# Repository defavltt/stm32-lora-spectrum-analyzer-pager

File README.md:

# STM32 based LoRa spectrum analyzer & pager

<!--  -->

## Features

 - Sending and receiving messages through LoRa
 
 - Configuring most of the RFM95's settings
 
 - Spectrum analyzer
 
 - Direct view of RFM95's registers
 
 - Battery measurement
 
 - Backlight
 
 - Vibration
 
 - Sleep modes
 
## Operation

 - Main menu is opened by pressing any button except multi key and escape

 - Stored messages can be seen by pressing multi key

 - Pressing and holding up / down automatically repeats the button

 - Waking up is done by pressing escape

 - Backlight is turned on / off by pressing and holding enter

## Menu description

### *All 10 menus (with the last one being an optional clock)*

### *Send message*

 - Screen is split into two halves
   - Text field
   - Scrollable keyboard with SEND / CLEAR / BACKSPACE buttons at the bottom

### *Display settings*

 - Backlight mode - timeout / no timeout (will not go to sleep) / on startup (turn backlight on when starting up)
 - Adjust contrast

### *RF settings*

 - Setting frequency
   - Select a digit to change by entering in the option and moving the digit cursor left / right
 - Continuous TX - doesnt transmit actual data, used for testing other devices

### *Feedback*

 - Select ringing type when a message is received - silent / single beep / beep & vibration / only vibration
 - Select key press feedback - silent / only click / click & vibration / only vibration

### *Sleep settings*

 - Enable / disable sleep
 - Enable / disable receiving (when enabled, device wakes up every 5 seconds to listen for a incoming message)

### *Battery level*

 - Shows battery level in volts

### *Spectrum analyzer*

 - Marker indicates RSSI for center frequency
 - 4 levels of vertical zooming
 - Navigation through parameters is done by pressing enter
 - Editing starting and ending frequency of the window
   - Up / down adjusts frequency by 1
   - Left / right adjusts frequency by 5
 - Showing parameters and/or marker is done by pressing multi key

### *Registers debug*

 - Top left number showing address of the first register of the group
 - Top right is showing current selected register in binary format
 - Values at left are registers in HEX format
 - Values at right are the addresses corresponding to the registers
 - Navigating the 8 register group is done by pressing up / down
 - Navigating outside of the group is done by pressing left / right

### *Save settings*

 - Saves settings into flash (don't overdo it to prevent flash memory wear)

### *Time and date*

 - Setting time
   - Select hour / minute by entering in the option, moving the digit cursor left / right and changing it by pressing up / down
 - Setting date
   - Select day / month / year by entering in the option, moving the digit cursor left / right and changing it by pressing up / down
 - Confirm by pressing enter on set time / date

 - *Requires an i2c clock board(MCP7940)*  

## Hardware

 - Parts
   - RFM95/SX1276 board
   - Tri-T D22-5003 B01 lcd screen (ks0713 driver)
   - STM32F103C8
   - 8Mhz crystal resonator
   - MCP1700 / MCP1703 3.3v regulator
   - AP2301 P channel MOSFETs used to drive vibrator and buzzer

Double sided board (bottom side freehand drawn with a permanent marker) with some wire jumpers required. Pads for keyboard, screen and optional serial are left. Parts from MT3608 are used for the backlight 8.2v power (only if the same screen is used - Tri-T D22-5003 B01 / driver - ks0713). Using a connector for plugging in an external antenna or a PA is encouraged.

This project uses:  
[Arduino Core STM32](https://github.com/stm32duino/Arduino_Core_STM32)  
[STM32 Low Power](https://github.com/stm32duino/STM32LowPower)  
[u8g2](https://github.com/olikraus/u8g2)  
a modified version of [RadioHead](https://www.airspayce.com/mikem/arduino/RadioHead)  
a modified version of [MCP7940](https://github.com/Zanduino/MCP7940)  

*MCX connector*

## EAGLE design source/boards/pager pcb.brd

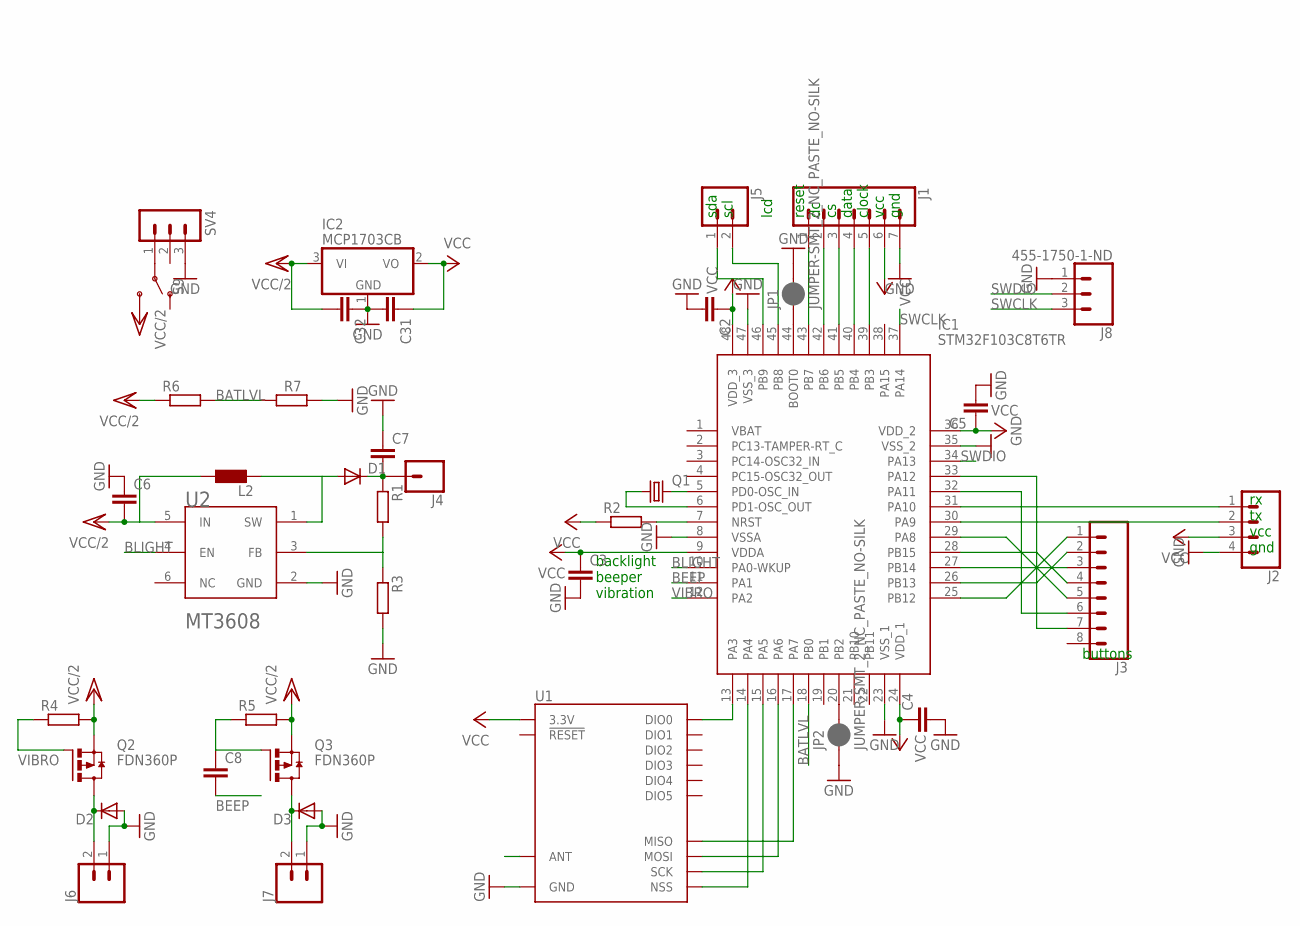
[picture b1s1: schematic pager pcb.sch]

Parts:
C2, C3, C4, C5, C6, C7, C8, C31, C32: C-EUC0805; C0805
D1, D2, D3: DIODE-DO-214AC; DO-214AC
IC1: STM32F103C8T6TR; QFP50P900X900X160-48N
IC2: MCP1703CB; SOT23
J1: CONN_07; 1X07
J2: CONN_04PTH; 1X04
J3: CONN_08"; 1X08
J4: CONN_01; 1X01
J5, J6, J7: CONN_02; 1X02
J8: 455-1750-1-ND; 1X03
JP1, JP2: JUMPER-SMT_2_NC_PASTE_NO-SILK; SMT-JUMPER_2_NC_PASTE_NO-SILK
L2: L0207/10; 0207/10
Q1: CRYSTALCTS406; CTS406
Q2, Q3: FDN360P; SUPER-SOT3
R1, R2, R3, R4, R5, R6, R7: R-EU_M0805; M0805
S9: SWITCH-SPDT-SMD-RIGHT-ANGLE; SWITCH_SPST_SMD_A
SV4: MA03-1
U1: RFM95W; RFM95/96/97/98W
U2: AEROSEMI_TECHNOLOGY_CO.,_LTD_MT3608AEROSEMI_TECHN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; AEROSEMI_TECHNOLOGY_CO.,_LTD_MT3608_0

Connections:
BATLVL: IC1.18 (PB0), R6.2, R7.1
BEEP: C8.2, IC1.11 (PA1)
BLIGHT: IC1.10 (PA0-WKUP), U2.4 (EN)
GND: C2.2, C3.2, C4.2, C5.2, C6.1, C7.1, C31.2, C32.1, D2.A, D3.A, IC1.8 (VSSA), IC1.23 (VSS_1), IC1.35 (VSS_2), IC1.47 (VSS_3), IC2.1 (GND), J1.7, J2.4, J6.1, J7.1, J8.1, JP1.2, JP2.1, R3.2, R7.2, SV4.3, U1.GND@1 (GND), U1.GND@2 (GND), U1.GND@3 (GND), U2.2 (GND)
unnamed: IC1.5 (PD0-OSC_IN), Q1.3 (2)
unnamed: IC1.6 (PD1-OSC_OUT), Q1.1
unnamed: IC1.7 (NRST), R2.2
unnamed: IC1.44 (BOOT0), JP1.1
unnamed: IC1.20 (PB2), JP2.2
unnamed: IC1.43 (PB7), J1.1
unnamed: IC1.42 (PB6), J1.2
unnamed: IC1.41 (PB5), J1.3
unnamed: IC1.40 (PB4), J1.4
unnamed: IC1.39 (PB3), J1.5
unnamed: IC1.31 (PA10), J2.1
unnamed: IC1.30 (PA9), J2.2
unnamed: IC1.17 (PA7), U1.MISO
unnamed: IC1.16 (PA6), U1.MOSI
unnamed: IC1.15 (PA5), U1.SCK
unnamed: IC1.14 (PA4), U1.NSS
unnamed: IC1.13 (PA3), U1.DIO0
unnamed: IC1.25 (PB12), J3.1
unnamed: IC1.26 (PB13), J3.2
unnamed: IC1.27 (PB14), J3.3
unnamed: IC1.28 (PB15), J3.4
unnamed: IC1.29 (PA8), J3.5
unnamed: IC1.33 (PA12), J3.7
unnamed: IC1.32 (PA11), J3.6
unnamed: D2.C, J6.2, Q2.3 (D)
unnamed: D3.C, J7.2, Q3.3 (D)
unnamed: IC1.46 (PB9), J5.1
unnamed: IC1.45 (PB8), J5.2
unnamed: S9.2, SV4.1
unnamed: D1.A, L2.2, U2.1 (SW)
unnamed: C7.2, D1.C, J4.1, R1.1
unnamed: C8.1, Q3.1 (G), R5.1
unnamed: R1.2, R3.1, U2.3 (FB)
SWCLK: IC1.37 (PA14), J8.3
SWDIO: IC1.34 (PA13), J8.2
VCC: C2.1, C3.1, C4.1, C5.1, C31.1, IC1.9 (VDDA), IC1.24 (VDD_1), IC1.36 (VDD_2), IC1.48 (VDD_3), IC2.2 (VO), J1.6, J2.3, R2.1, U1.3.3V
VCC/2: C6.2, C32.2, IC2.3 (VI), L2.1, Q2.2 (S), Q3.2 (S), R4.2, R5.2, R6.1, S9.3 (S), U2.5 (IN)
VIBRO: IC1.12 (PA2), Q2.1 (G), R4.1

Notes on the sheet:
buttons
backlight beeper vibration
rx tx vcc gnd
lcd reset dc cs data clock vcc gnd
sda scl

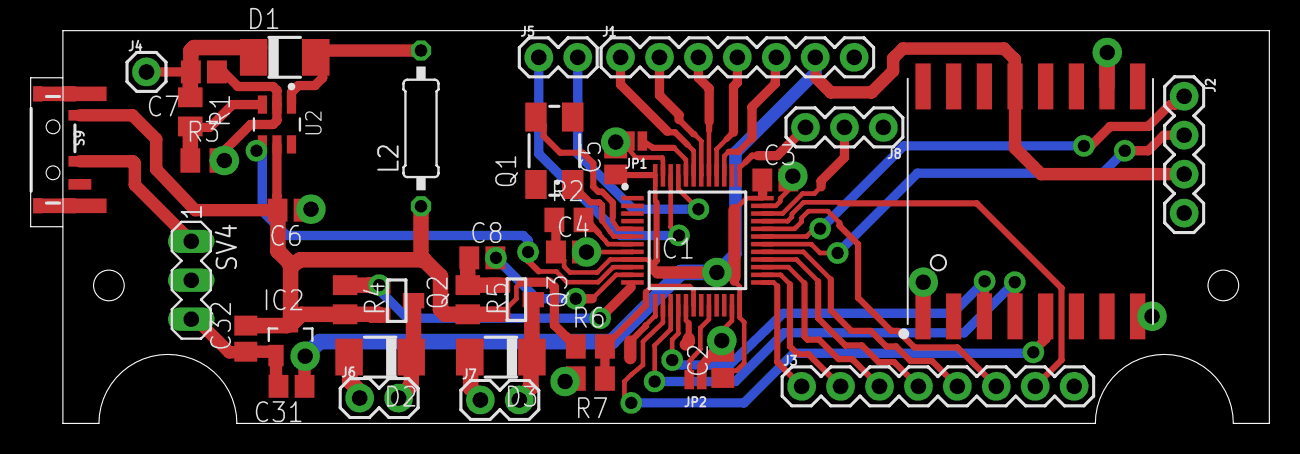
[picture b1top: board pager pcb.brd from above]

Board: 2 copper layers, 80.8 x 25.6 mm, 39 parts (0 on the bottom side), 42 nets.

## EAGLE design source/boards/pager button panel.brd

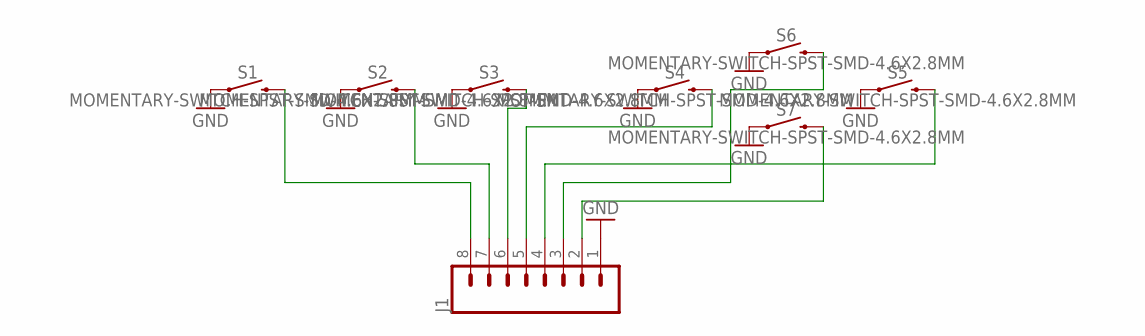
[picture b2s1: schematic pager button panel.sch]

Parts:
J1: CONN_08"; 1X08
S1, S2, S3, S4, S5, S6, S7: MOMENTARY-SWITCH-SPST-SMD-4.6X2.8MM; TACTILE_SWITCH_SMD_4.6X2.8MM

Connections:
GND: J1.1, S1.1, S1.2 (1), S2.1, S2.2 (1), S3.1, S3.2 (1), S4.1, S4.2 (1), S5.1, S5.2 (1), S6.1, S6.2 (1), S7.1, S7.2 (1)
unnamed: J1.8, S1.3 (2), S1.4 (2)
unnamed: J1.7, S2.3 (2), S2.4 (2)
unnamed: J1.6, S3.3 (2), S3.4 (2)
unnamed: J1.5, S4.3 (2), S4.4 (2)
unnamed: J1.4, S5.3 (2), S5.4 (2)
unnamed: J1.3, S6.3 (2), S6.4 (2)
unnamed: J1.2, S7.3 (2), S7.4 (2)

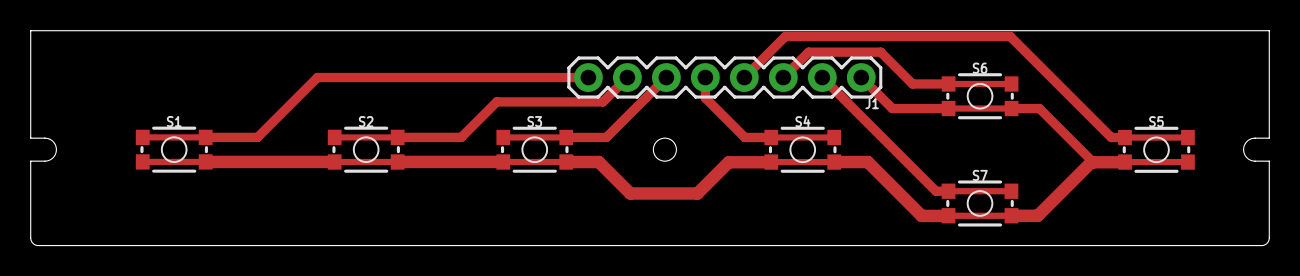
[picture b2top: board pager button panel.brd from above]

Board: 2 copper layers, 80.7 x 14.0 mm, 8 parts (0 on the bottom side), 8 nets.

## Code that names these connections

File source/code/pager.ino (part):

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#include <Arduino.h>
#include <U8g2lib.h>

U8G2_ST7565_KS0713_F_4W_SW_SPI u8g2(U8G2_R0, /* clock=*/ PB3, /* data=*/ PB4, /* cs=*/ PB5, /* dc=*/ PB6, /* reset=*/ PB7);    // KS0713 controller

#include "xbm.h"

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#include <RH_RF95.h>
#include <RHSoftwareSPI.h>
RHSoftwareSPI spi;
RH_RF95 rf95(PA4, PA3, spi); //NSS, DIO0

char messagebuf1[30], messagebuf2[30], messagebuf3[30], messagebuf4[30], messagebuf5[30], messagebuf6[30], messagebuf7[30], messagebuf8[30];

#define one_(state) if(digitalRead(PB12) == LOW && digitalRead(PB12) != state) { statebuffer = 1; } else { statebuffer = 0; }  state = digitalRead(PB12);
#define two_(state) if(digitalRead(PB13) == LOW && digitalRead(PB13) != state) { statebuffer = 1; } else { statebuffer = 0; }  state = digitalRead(PB13);
#define three_(state) if(digitalRead(PB14) == LOW && digitalRead(PB14) != state) { statebuffer = 1; } else { statebuffer = 0; }  state = digitalRead(PB14);
#define left_(state) if(digitalRead(PB15) == LOW && digitalRead(PB15) != state) { statebuffer = 1; } else { statebuffer = 0; }  state = digitalRead(PB15);
#define right_(state) if(digitalRead(PA8) == LOW && digitalRead(PA8) != state) { statebuffer = 1; } else { statebuffer = 0; }  state = digitalRead(PA8);
#define up_(state) if(digitalRead(PA11) == LOW && digitalRead(PA11) != state) { statebuffer = 1; } else { statebuffer = 0; }  state = digitalRead(PA11);
#define down_(state) if(digitalRead(PA12) == LOW && digitalRead(PA12) != state) { statebuffer = 1; } else { statebuffer = 0; }  state = digitalRead(PA12);

static const unsigned char unreadicon[] U8X8_PROGMEM = { //12x7
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byte freqadjust;

byte feedbackmode = 1;
byte msgalert = 2; //1 - silent, 2 - beep, 3 - beep & vibro, 4 - vibro, 5 - single beep
byte bfeedback = 4; //1 - silent, 2 - click, 3 - click & vibro, 4 - vibro
bool sleepenable = 1;
bool sleepreceiving = 1;
bool sleeping;
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} settings;

void setup() {
  pinMode(PA0, OUTPUT); //backlight
//  digitalWrite(PA0, HIGH);

  pinMode(PA1, OUTPUT); //beeper
  digitalWrite(PA2, HIGH);

  pinMode(PA2, OUTPUT); //vibrator
  digitalWrite(PA2, HIGH);

  pinMode(PB12, INPUT_PULLUP); //1
  pinMode(PB13, INPUT_PULLUP); //2
  pinMode(PB14, INPUT_PULLUP); //3
  pinMode(PB15, INPUT_PULLUP); //left
  pinMode(PA8, INPUT_PULLUP); //right
  pinMode(PA11, INPUT_PULLUP); //up
  pinMode(PA12, INPUT_PULLUP); //down

  pinMode(PB0, INPUT); //measure battery
  
  u8g2.begin();
  u8g2.setFont(u8g2_font_6x12_tr);
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  rf95.setPreambleLength(preamble);
  rf95.setModemConfig(RH_RF95::Bw31_25Cr48Sf512);

  if(!digitalRead(PA8)) { //jam mode //hold right at startup
    rf95.setSpreadingFactor(11); //6-12 //saw frequency
    rf95.setSignalBandwidth(500000); //0.5mhz bandwidth
    rf95.setPreambleLength(0xffff); //max
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  delay(200);

  LowPower.begin();
  LowPower.attachInterruptWakeup(PB14, wakeup, FALLING, SLEEP_MODE);

  MCP7940.begin(); //PA10 - sda, PA9 - scl
//  while (!MCP7940.deviceStatus()) {
//    bool deviceStatus = MCP7940.deviceStart();  // Start oscillator and return state
//    if (!deviceStatus) {                        // If it didn't start
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    one = 1;
    lastbuttonpressed = 1;
  }
  if(!digitalRead(PB12)) { //hold one, turn on/off backlight
    holdtimer++;
    if(holdtimer == 1200) {
      enablebacklight = !enablebacklight;
      digitalWrite(PA0, enablebacklight);
    }
    delay(1);
  } else {
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    down = 1;
    lastbuttonpressed = 7;
  }
  if(!digitalRead(PB12) && !digitalRead(PB14) && !digitalRead(PA8)) { //play startup splash with button combo (one, three, right)
    digitalWrite(PA2, HIGH); //turn off vibrator
//    playstartupsplash();
  }

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    currentmillisbl = millis(); //reset backlight timer
    currentmillisheld = millis(); //reset button hold timer
    beepcount = 0; //stop alerting
    batterylevel = analogRead(PB0); //read battery level
  }

  if(digitalRead(PB15) == LOW || digitalRead(PA8) == LOW || digitalRead(PA11) == LOW || digitalRead(PA12) == LOW) {
    if(millis() >= currentmillisheld + 800) { //amount of time for nav buttons to be held
      globalbuttonsheld = 1;
    }
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//    buttonfeedback();

    if(bfeedback == 2 || bfeedback == 3) {
      tone(PA1, 4000, 20);
    }
    updatescreen = 1;
    currentmillissleep = millis(); //reset sleep timer
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    u8g2.sendBuffer();
  }

//  digitalWrite(PA0, enablebacklight);

  if(vibration) {
    digitalWrite(PA2, LOW); //start vibration
    if(millis() >= currentmillisvibro + 140) {
      digitalWrite(PA2, HIGH); //end vibration
      vibration = 0;
    }
  }
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      case 1: //timeout
        if(millis() >= currentmillisbl + 8000) {
          enablebacklight = 0;
          digitalWrite(PA0, enablebacklight);
        }
        break;
      case 2: //no timeout
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    if(millis() >= currentmillissleep + 20000) { //go to sleep
      while(true) { //forever loop
        u8g2.clearBuffer();
        batterylevel = analogRead(PB0); //read battery level
        if(batterylevel <= 440) {
          tone(PA1, 2000, 100);
        }
        showstatusicons();
        u8g2.sendBuffer();
  
        enablebacklight = 0;
        digitalWrite(PA0, LOW); //turn off backlight
        digitalWrite(PA2, HIGH); //turn off vibrator

        sleeping = 1; //sleep status

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  
//        LowPower.deepSleep(30000); //wake up at 30s intervals
        
        if(digitalRead(PB14) == LOW || sleeping == 0) {
          currentmillissleep = millis(); //reset timer
          sleeping = 0; //sleep status
          break; //exit out of forever loop
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  if(transmit) {
    rf95.send((uint8_t* )writemsgbuffer, writemsgbuffer_.length()+1); //send the message
    transmit = 0; //so it doesnt transmit again
    tone(PA1, 2000, 40);
  }
  
  resetstates(); //reset states at loop end
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
void buttonfeedback() {
  if(bfeedback == 2 || bfeedback == 3) {
    tone(PA1, 4000, 35);
  }
  if(bfeedback == 3 || bfeedback == 4) {
    currentmillisvibro = millis(); //set currentmillisvibro before vibration
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    currentmillisalert = millis();
    
    if(msgalert == 2 || msgalert == 3) {
      tone(PA1, beepseq[beepcount-1], 300);
    }
    if(msgalert == 3 || msgalert == 4) {
      if(vibroseq[beepcount-1]) {
        digitalWrite(PA2, LOW);
      } else {
        digitalWrite(PA2, HIGH);
      }
    }
    beepcount++;
    if(msgalert == 5) {
      tone(PA1, 4000, 300);
      beepcount = 0; //single beep
    }
  }
}
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}

void playstartupsplash() {
  digitalWrite(PA0, HIGH); //turn on backlight
  for(byte i = 4; i < 10; i++) { //startup splash
    u8g2.clearBuffer();
    switch(i) {
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    delay(50);
  }
  delay(1000);
  digitalWrite(PA0, LOW); //turn off backlight
}

bool bitread(byte value, byte select) {
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
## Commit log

2025-01-29 OLD BAD CODE

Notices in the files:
parts and their libraries:
SparkFun-Switches: Licensing: Creative Commons ShareAlike 4.0 International - https://creativecommons.org/licenses/by-sa/4.0
